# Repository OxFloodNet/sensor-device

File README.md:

#OxFloodNet Sensor Device

Sensor code (originally started at Sushack 2013 - http://www.sushack.co.uk/)
## Requirements
Base components:
 * Ciseco RFu-328 (SRF radio + ATMega328 module) with an ultrasonic sensor
 * Schematic and parts list shown in [PCB directory](https://github.com/OxFloodNet/sensor-device/tree/master/PCB)

## Output 
 * LLAP to transmit sensor readings
 * Sends messages in format: a<device ID><sensor ID><value><dash padding til 12 chars>
 * Example message: aR1U65------
 * Meaning: Device R1, Ultrasonic Sensor, Reading: 65cm to water surface.
 * Example message: aR1B5500----
 * Meaning: Device R1, Battery sensor, Reading: 5500mV (5.5v remaining in battery)
 
Typical sensor deployment

Testing

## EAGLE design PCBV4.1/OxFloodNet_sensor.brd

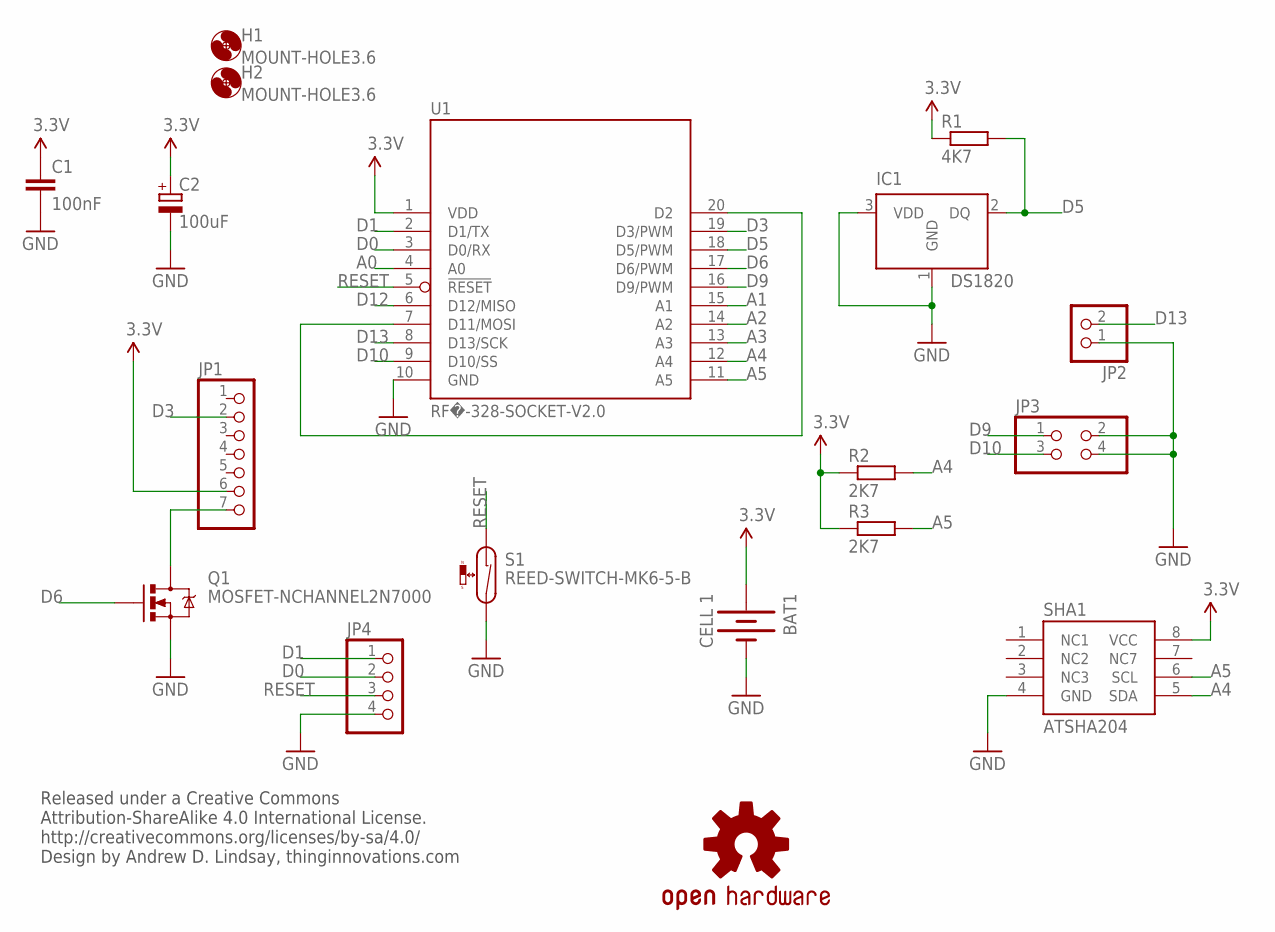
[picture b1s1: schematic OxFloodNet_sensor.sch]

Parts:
BAT1: CELL 1; BATTERY-AA
C1: 100nF; C025-024X044
C2: 100uF; E2,5-6E
H1, H2: MOUNT-HOLE3.6; 3,6
IC1: DS1820; TO-92
JP1: 1X07
JP2: 1X02
JP3: 2X02
JP4: PINHD-1X4; 1X04
LOGO1: OSHW-LOGOM; OSHW-LOGO-M
Q1: MOSFET-NCHANNEL2N7000; TO-92
R1: 4K7; 0207/7
R2, R3: 2K7; 0207/7
S1: REED-SWITCH-MK6-5-B; MK6-5
SHA1: ATSHA204; SOIC8
U1: RF�-328-SOCKET-V2.0; RF�-SOCKET-V2.0

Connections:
3.3V: BAT1.PWR@1 (+), C1.1, C2.+, JP1.6, R1.1, R2.1, R3.1, SHA1.8 (VCC), U1.1 (VDD)
A0: U1.4 (A0)
A1: U1.15 (A1)
A2: U1.14 (A2)
A3: U1.13 (A3)
A4: R2.2, SHA1.5 (SDA), U1.12 (A4)
A5: R3.2, SHA1.6 (SCL), U1.11 (A5)
D0: JP4.2, U1.3 (D0/RX)
D1: JP4.1, U1.2 (D1/TX)
D3: JP1.2, U1.19 (D3/PWM)
D5: IC1.2 (DQ), R1.2, U1.18 (D5/PWM)
D6: Q1.2 (G), U1.17 (D6/PWM)
D9: JP3.1, U1.16 (D9/PWM)
D10: JP3.3, U1.9 (D10/SS)
D12: U1.6 (D12/MISO)
D13: JP2.2, U1.8 (D13/SCK)
GND: BAT1.GND@1 (-), C1.2, C2.-, IC1.1 (GND), IC1.3 (VDD), JP2.1, JP3.2, JP3.4, JP4.4, Q1.1 (S), S1.2, SHA1.4 (GND), U1.10 (GND)
unnamed: U1.7 (D11/MOSI), U1.20 (D2)
unnamed: JP1.7, Q1.3 (D)
RESET: JP4.3, S1.1, U1.5 (!RESET)

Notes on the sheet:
Released under a Creative Commons Attribution-ShareAlike 4.0 International License. http://creativecommons.org/licenses/by-sa/4.0/ Design by Andrew D. Lindsay, thinginnovations.com

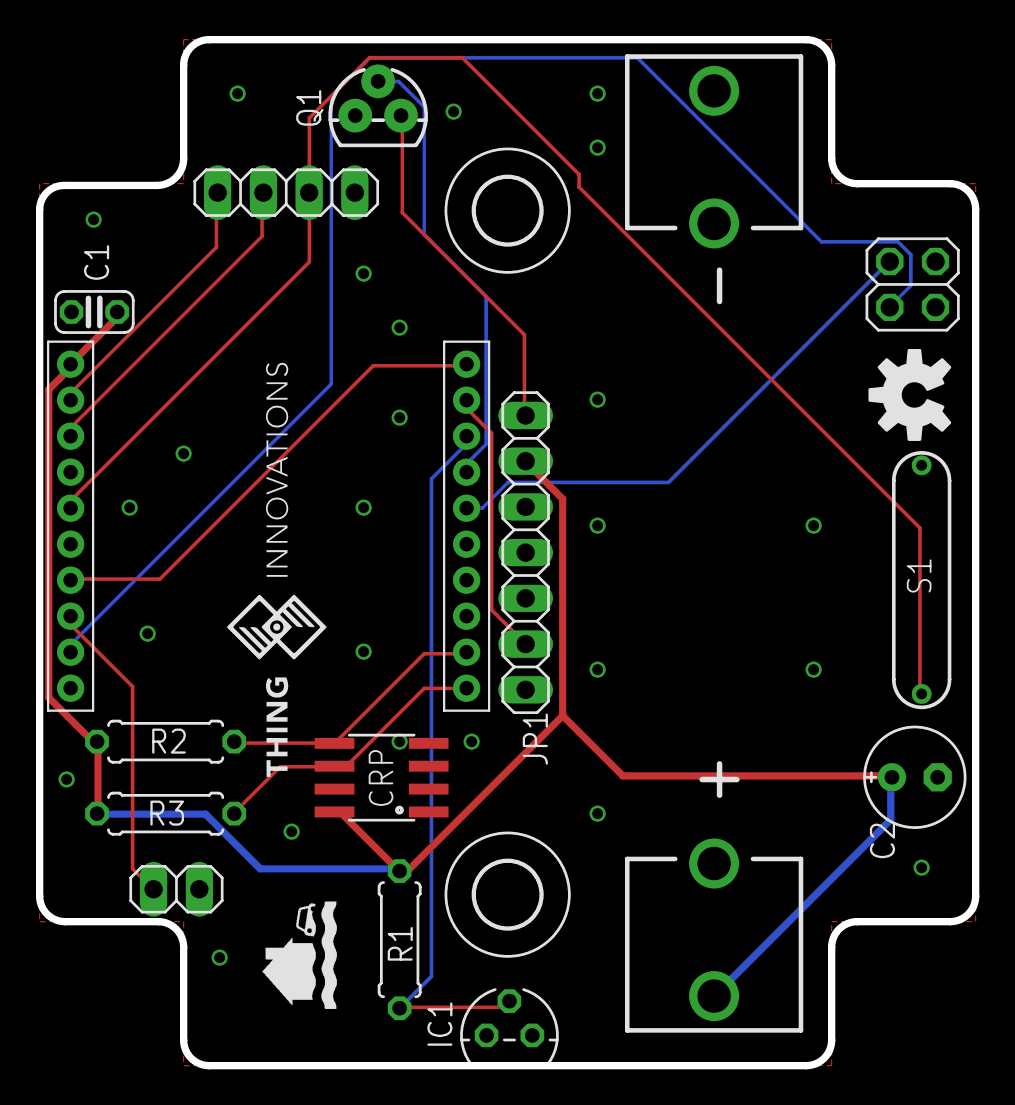
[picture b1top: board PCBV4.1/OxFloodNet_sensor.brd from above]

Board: 2 copper layers, 52.0 x 57.0 mm, 19 parts (0 on the bottom side), 15 nets.

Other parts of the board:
U$1: THING_INNOVATIONS_SMALL

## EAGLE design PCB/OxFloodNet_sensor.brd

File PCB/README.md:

This repository contains the EAGLE files and gerbers for creating an Oxfloodnet Sensor PCB v3.1. 

The sensor device has the following features:
* Arduino-compatible code wireless sensor node
* Wireless
  * Transmits using 433, 868 or 915* MHz  (*USA only)
  * LLAP Protocol
  * Up to 200m range
  * Chip, Wire Whip and External (u.FL) antenna options
* Power: 
  * Option for Long-life (1 x 3.6v Tadiran Lithium Cell) or Off-the Shelf (2 x 1.6v AA Batteries)
  * Battery voltage reading sent every 10th cycle
  * Extremely low power sleep mode (~30uA)
* Maxbotix ultrasonic ranger
  * Compatible with most Maxbotix sensors
  * Maxbotix MB7060 XL-MaxSonar-WR1 IP67 outdoor-rated sensor recommended due to humidity/condensation issues
  * Maxbotix MB1230 works but has condensation issues above streams
* DS18B20 temperature sensor 
  * to compensate for speed of sound in different conditions
  * Temperature data also a useful byproduct
  * Molex header connection to board for easy maintenance
* Jumpers/Headers
  * Control poll cycle (10s, 5, 10 or 15 minutes depending on jumpers)
  * FTDI connector for programming sketch to RFu-328 (not powered)
  * Molex temperature connector
  * Maxbotix 7-way header
  
See Arduino [device code](https://github.com/OxFloodNet/sensor-device/tree/master/OxFloodNet_Sensor) for more specific info about controlling these.

A schematic of the Oxfloodnet Sensor PCB v3.1  

The assembled v3.0 sensor can be seen in the pictures below along with aseembly instructions at [http://blog.thiseldo.co.uk/?p=1285](http://blog.thiseldo.co.uk/?p=1285). V3.1 assembly is similar, instructions will follow later.

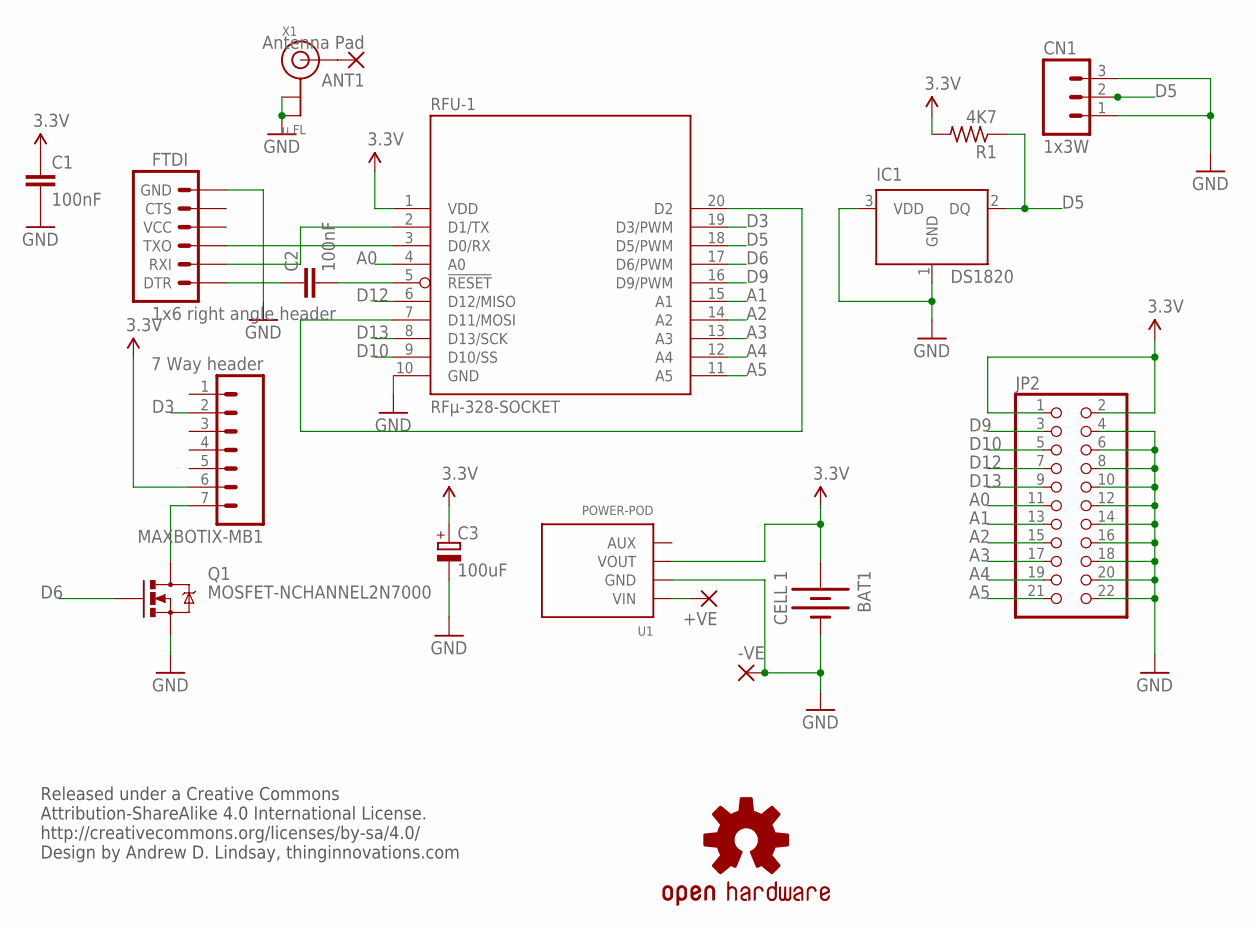
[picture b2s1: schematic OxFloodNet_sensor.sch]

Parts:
+VE: 2,54/0,8
-VE: 2,54/0,8
ANT1: Antenna Pad; 2,54/0,8
BAT1: CELL 1; BATTERY-AA
C1, C2: 100nF; C025-024X044
C3: 100uF; E2,5-6E
CN1: 1x3W; 1X03
FTDI: 1x6 right angle header; 1X06_LONGPADS
IC1: DS1820; TO-92
JP2: PINHD-2X11; 2X11
LOGO1: OSHW-LOGOM; OSHW-LOGO-M
MAXBOTIX-MB1: 7 Way header; 1X07_LONGPADS
Q1: MOSFET-NCHANNEL2N7000; TO-92
R1: 4K7; 0207/7
RFU-1: RFµ-328-SOCKET
U1: POWER-POD; POWER-POD-LANDING
X1: u.FL; U.FL

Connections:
3.3V: BAT1.PWR@1 (+), C1.1, C3.+, JP2.1, JP2.2, MAXBOTIX-MB1.6, R1.2, RFU-1.1 (VDD), U1.3 (VOUT)
A0: JP2.11, RFU-1.4 (A0)
A1: JP2.13, RFU-1.15 (A1)
A2: JP2.15, RFU-1.14 (A2)
A3: JP2.17, RFU-1.13 (A3)
A4: JP2.19, RFU-1.12 (A4)
A5: JP2.21, RFU-1.11 (A5)
D3: MAXBOTIX-MB1.2, RFU-1.19 (D3/PWM)
D5: CN1.2, IC1.2 (DQ), R1.1, RFU-1.18 (D5/PWM)
D6: Q1.2 (G), RFU-1.17 (D6/PWM)
D9: JP2.3, RFU-1.16 (D9/PWM)
D10: JP2.5, RFU-1.9 (D10/SS)
D12: JP2.7, RFU-1.6 (D12/MISO)
D13: JP2.9, RFU-1.8 (D13/SCK)
GND: -VE.1, BAT1.GND@1 (-), C1.2, C3.-, CN1.1, CN1.3, FTDI.6 (GND), IC1.1 (GND), IC1.3 (VDD), JP2.4, JP2.6, JP2.8, JP2.10, JP2.12, JP2.14, JP2.16, JP2.18, JP2.20, JP2.22, Q1.1 (S), RFU-1.10 (GND), U1.2 (GND), X1.1 (GND), X1.2 (GND)
unnamed: RFU-1.7 (D11/MOSI), RFU-1.20 (D2)
unnamed: MAXBOTIX-MB1.7, Q1.3 (D)
unnamed: +VE.1, U1.1 (VIN)
unnamed: C2.2, RFU-1.5 (!RESET)
unnamed: C2.1, FTDI.1 (DTR)
unnamed: FTDI.2 (RXI), RFU-1.2 (D1/TX)
unnamed: FTDI.3 (TXO), RFU-1.3 (D0/RX)
unnamed: ANT1.1, X1.3 (SIGNAL)

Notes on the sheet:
Released under a Creative Commons Attribution-ShareAlike 4.0 International License. http://creativecommons.org/licenses/by-sa/4.0/ Design by Andrew D. Lindsay, thinginnovations.com

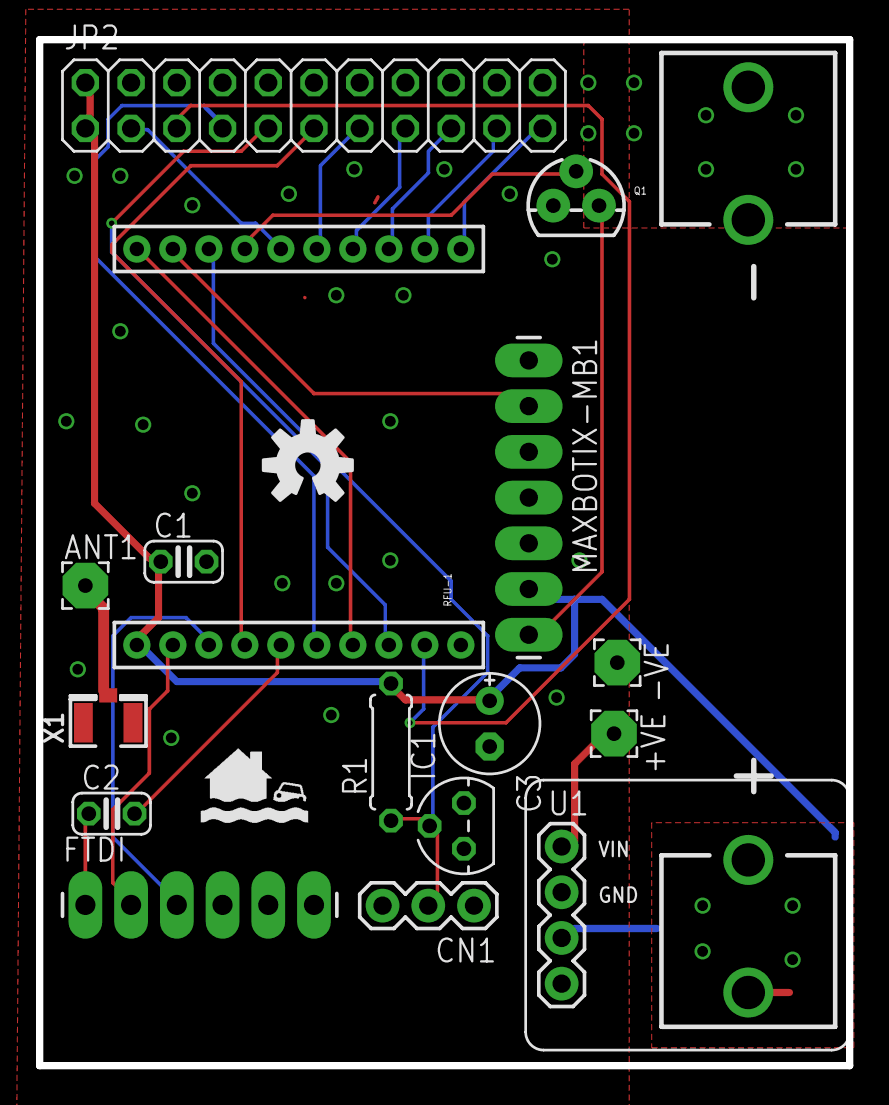
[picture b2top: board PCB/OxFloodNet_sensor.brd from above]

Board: 2 copper layers, 45.0 x 57.0 mm, 18 parts (0 on the bottom side), 23 nets.

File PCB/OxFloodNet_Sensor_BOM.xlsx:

Oxford Flood Network Sensor: Bill of materials |  |  |  |  | Cost exclude VAT
Version: | V3.1 | Farnell parts are suggestions, other sources may be cheaper. |  |  | Total | 110.54000000000002
 | External Antenna | Yes
 | Power Source | 3.6V Tadiran
Part Number | Value | Quantity | Supplier | Supplier Part No. | Unit Cost | Cost
pcb1 | PCB, V3.0 | 1 | Thing Innovations | PCBOFN3.1 | 1.5 | 1.5
C1, C2 | 100nF Ceramic multilayer | 2 | Farnell | 2309020 | 0.28999999999999998 | 0.57999999999999996
C3 | 100uF Electrolytic 16V, D6.3xH11 Pitch2.5 | 1 | Farnell | 1144614 | 0.2 | 0.2
CN1 | 1x3W Right angle Header pins | 1 | Farnell | 2356177 | 0.22 | 0.22
CN2 | 1x3W Header | 1 | Farnell | 1098033 | 0.52 | 0.52
FTDI | 1x6W Right angle Header pins | 1 | Farnell | 2356180 | 0.51 | 0.51
JP2 | 2x11W Pin Header pins | 1 | Farnell | 2356134 (2x12W, cut down) | 0.73 | 0.73
IC1 | DS18B20 - 1-Wire Digital Thermometer | 1 | Farnell | 1187948 | 4.13 | 4.13
MAXBOTIX-MB1 | 1x7W Header | 1 | Farnell | 1098037 | 1.1200000000000001 | 1.1200000000000001
 | 1x7W Right Angle Header pins | 1 | Farnell | 2356182 | 0.65 | 0.65
Q1 | 2N7000 Mosfet-N Channel | 1 | Farnell | 9845178 | 0.09 | 0.09
R1 | 4K7, 1/4W Resistor | 1 | Farnell | 2329534 | 0.02 | 0.02
SKT1,2 | 10w 2mm socket | 2 | Farnell | 1109732 | 2.08 | 4.16
U$1 | RFµ-328 | 1 | Ciseco | RFµ-328 | 11.66 | 11.66
SENSOR1 | Maxbotix MB7060 XL-MaxSonar-WR1, Standard edition | 1 | Technobots online | Maxbotix MB7060 XL-MaxSonar-WR1 | 64 | 64
 | WR Mounting Hardware, Maxbotix MB7950 | 1 | Technobots online | Maxbotix MB7950 | 1.73 | 1.73
 | 20cm hookup wire, 0.2mm2, blue | 1 |  | Cost for guidance only | 0.2 | 0.2 | Only availble in min 1m lengths or reels from Farnell.
 | 20cm hookup wire, 0.2mm2, brown | 2 |  | Cost for guidance only | 0.2 | 0.4 | Only availble in min 1m lengths or reels from Farnell.
 | 2mm Heatshrink tubing, 5cm | 1 |  | Cost for guidance only | 0.2 | 0.2 | Only availble in min 1m lengths or reels from Farnell.
 | 4mm Heatshrink tubing, 2cm | 1 |  | Cost for guidance only | 0.2 | 0.2 | Only availble in min 1m lengths or reels from Farnell.
 | IP55 Enclosure Grey 85 x 75 x 65mm. | 1 | Screwfix | Stock No: 33991 | 2.91 | 2.91
95.730000000000018
External Antenna - Additional Parts
X1 | u.FL Antenna Connector | 1 | Ciseco | u.FL Antenna Connector | 1 | 1
 | u.FL Antenna to SMA pigtail | 1 | Ciseco | u.FL Antenna to SMA pigtail | 3.33 | 3.33
PAD1 | 1w 2mm socket & Pin | 1 | Farnell | 1109732 and 2289780 10w cut down | 1.59 | 1.59 | Use 2 x 1109732 and 1 x 2289780 per 10 units
ANT | External Antenna | 1 | SK Pang | ANT-900MR | 5 | 5
10.92
3.6V Single AA Cell power option
BAT1 | AA Snap in Battery clip | 2 | Farnell | 908733 - Pack of 5 | 0.2 | 0.4
 | 3.6V Tadiran SL-760 AA | 1 | Battery Station | SL-760 AA | 3.49 | 3.49
3.89
Dual Cell AA power option
 | 2xAA battery holder with leads | 1 | Farnell | 1702631 | 0.99 | 0.99
 | 1x4W Header | 1 | Farnell | 1098034 | 0.78 | 0.78
U1 | PowerPOD NCP1402 3V3 | 1 | Ciseco | PowerPOD NCP1402 3V3 | 4.16 | 4.16
5.93

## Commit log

2014-03-23 Added images of custom PCB
    Andrew Lindsay's custom PCB photos
2014-03-23 Updated readme
    Copied from sushack page
2014-03-23 Files uploaded
2014-03-23 More files uploaded
2014-03-23 Readme to show Images
2014-03-23 Created readme with details of schematic & code
2014-03-23 Added note about schematic bug
2014-03-30 Uploaded schematic
2014-03-30 First commit of sensor firmware
2014-03-30 Added OneWire and DallasTemperature libraries for convenience
2014-03-30 Added libraries
2014-03-30 Not needed
2014-03-30 Deprecated this version
2014-03-30 updates to msg and polling
2014-04-12 New demo code
2014-04-12 Updated temp compensation, added temp msg
2014-05-10 Changed Node ID
    Probably needs to be in a separate variables file
2014-05-10 Deprecation notes
2014-05-12 test
2014-07-01 Cleanup latest code
2014-07-01 cleanup
2014-07-14 add eagle files
2014-07-14 new images
2014-07-14 latest checkin
2014-07-26 Image of PCB
    Created Image file from EAGLE
2014-07-26 Major readme update
    Includes version number, board features, options, link to assembly guide.
2014-07-26 Sensor models added
2014-07-27 Updated to v3.1
2014-07-27 updated info
2014-08-11 Sensor BOM minor change
2014-08-11 Parts List obsolete, see XLS with list in
2014-08-11 Added Build Guide GIF
2014-08-13 Added build guide
2014-08-17 Updated for V3.1 PCB
2014-08-17 Added readme
2014-09-11 Repeat STARTED message x3
2014-09-11 Added Debug Info & Initial Distance Reading
    Set STARTED message to show for 5 x 1 second at start.
    Moved sleep to the end of the main loop, meaning we get an initial
    distance reading.
    Also, serial debug info sent at the start with labels.
2014-09-11 Cleaned up Jumper settings
2014-09-11 Updated version number to 3.1.2
2014-09-11 Updated Inventory
2014-09-11 Clarification on sensor ID
2014-09-11 Commented out data rate change
    Attempted to sent ATDR3 - to set lower data rate. Unsuccessful.
2014-09-11 Added image to help explain jumpers
2014-09-11 Commentary added to explain jumpers
2014-09-11 Added image & explanation
2014-09-11 Made Battery reading not mutually exclusive
    Distance reading now happens after battery reading, where before it was
    not performed when a battery reading was done.
2014-09-11 Improvements to docs
2014-09-18 minor readability change
2014-09-28 v3.1.3 tidy up & version number broadcast
    1) Tidy of code to help me understand it.
    2) SRF now transmits VERx.x.x when it starts up - needs to be added to
    the list of message types
2014-09-28 Revert "v3.1.3 tidy up & version number broadcast"
    This reverts commit 93fb807c3dc9b83a4bc0ffd53110faf6d76fad14.
2014-10-06 Updated after feedback, added new steps
2014-10-25 just save it somewhere
2014-10-26 Updates for variable startup polling
2014-10-26 Updates and corrections
2014-11-05 blah
2014-11-05 Revert "blah"
    This reverts commit af2f7e4be876e748c6b9e79469db28d9827ce941.
2014-11-05 Testing new tag release
2014-11-05 Mad change
2014-11-05 mad stuff
2014-11-07 Sync version numbers
2014-11-07 Made battery reading not mutually exclusive
    Previously battery reading was performed instead of distance reading
    every nth cycle. It's now sent at the same time to ensure no gaps in the
    flood data.
2014-11-07 Changes for readability
    Recommitted changes from 1 month ago
2014-11-07 Minor cosmetic changes
2015-02-12 Revert "Minor cosmetic changes"
    This reverts commit a531f91a140690f56efd068e64f48305b640f9c5.
2015-02-12 Revert "Revert "Minor cosmetic changes""
    This reverts commit 9d371e099d15d4934ee6fa9f83dfeda429142db9.
2015-02-12 Version 3.1.5 - Fixes for temperature compensation
    New version fixes temperature compensation bug.
2015-04-10 Change to readme
2015-05-21 Added V4.1 sensor PCB and code
2015-05-22 Added sample NR flow
2015-05-25 Renamed main sketch
2015-05-27 Corrected node ID conversion
2015-06-09 Create LICENSE.md
    Clarifying licences
2015-06-09 Checkin BOM
    BOM
2015-06-10 Added long pins header
2015-06-10 additonal notes
2015-06-19 Added LLAPExtended library
2015-08-17 LCD Display
    Added LCD Display sketch for using as a test device.
2015-08-23 Refactoring
    Refactoring parts of code to reduce both Flash and RAM footprint and
    get rid of duplicate code.

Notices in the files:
parts and their libraries:
SparkFun-Connectors: Licensing: CC v3.0 Share-Alike You are welcome to use this library for commercial purposes.
